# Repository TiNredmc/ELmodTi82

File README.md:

# ELmodTi82
EL backlight mod for TI-82. This Repo includes Schematic, PCB and BOMs.

# BOM (can be found cheaply on Aliexpress)
1. x1 HV823LG EL panel driver (https://www.aliexpress.com/item/4000117958037.html?spm=a2g0s.9042311.0.0.1d8e4c4dCgCwEE)
2. x1 1N4148 SOD-123 diode (https://www.aliexpress.com/item/32947085991.html?spm=a2g0s.12269583.0.0.7d003e51weey3z) select 1n4148 SOD-123
3. x1 10nF (0.01uF) 100V THT Polypropylene Film (https://www.aliexpress.com/item/4000051926991.html?spm=a2g0s.9042311.0.0.1d8e4c4dCgCwEE) select 10NF
4. x1 1nF 16V smd 0603 (https://www.aliexpress.com/item/33009930741.html?spm=a2g0s.9042311.0.0.1d8e4c4dCgCwEE) select 1nF
5. x1 750kOhm smd 0603 (https://www.aliexpress.com/item/32951328488.html?spm=a2g0s.9042311.0.0.1d8e4c4dCgCwEE) select 750k
6. x1 2MOhm smd 0603 (https://www.aliexpress.com/item/32951328488.html?spm=a2g0s.9042311.0.0.1d8e4c4dCgCwEE) Select 2M
7. x1 560uH 50mA smd 1812 (https://www.aliexpress.com/item/33036139022.html?spm=a2g0s.9042311.0.0.1d8e4c4dCgCwEE)
8. x1 10x10cm EL Panel (can be cut into the same size as the display, Will update later when I teardown my cal, roughtly 4cm x 6.5cm) (https://www.aliexpress.com/item/32689125682.html?spm=a2g0s.9042311.0.0.1d8e4c4dCgCwEE) 

# PCB
V1 https://oshpark.com/shared_projects/CnYBnhLE , V2 https://oshpark.com/shared_projects/YBjWS07Q

# UPDATE 1 (2020/3/5)
I just confused thinking that I order the SOD-123 but it's turn out to be SOD-323 which is smaller, but from online lookup on Google. they still some different but you (and me) can actually solder this tiny, by just put it in center and put LOADS of solder to hold it.

# UPDATE2 (2020/3/5)
I just confused again.... the SOD-123 is actually available and I order the SOD-123 🤦‍

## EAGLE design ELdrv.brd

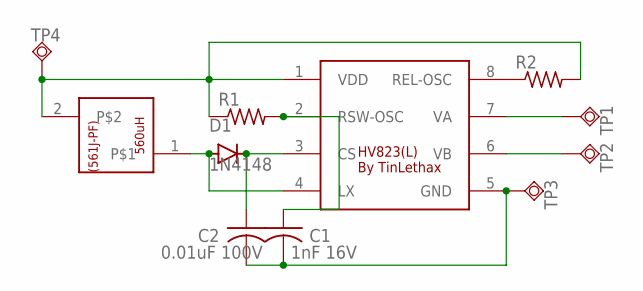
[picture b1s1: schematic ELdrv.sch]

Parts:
C1: 1nF 16V; C0603K
C2: 0.01uF 100V; C025-040X050
D1: 1N4148; SOD-123_MINI-SMA
R1, R2: R-US_R0603; R0603
TP1, TP2, TP3, TP4: TPSQTP20SQ; TP20SQ
U$1: HV823; SOIC127P600X175-9T200L
U$2: NL453232T-561J-PF; INDC4526X50N

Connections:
unnamed: D1.A, U$1.4 (LX), U$2.1
unnamed: C2.1, D1.C, U$1.3 (CS)
unnamed: R1.1, R2.2, TP4.TP, U$1.1 (VDD), U$2.2
unnamed: C1.1, R1.2, U$1.2 (RSW-OSC)
unnamed: R2.1, U$1.8 (REL-OSC)
unnamed: C1.2, C2.2, TP3.TP, U$1.5 (GND)
unnamed: TP1.TP, U$1.7 (VA)
unnamed: TP2.TP, U$1.6 (VB)

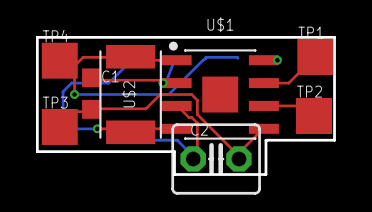
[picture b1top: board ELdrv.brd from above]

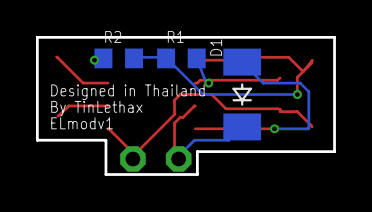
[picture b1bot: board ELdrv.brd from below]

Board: 2 copper layers, 16.5 x 7.6 mm, 11 parts (3 on the bottom side), 8 nets.

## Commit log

2020-03-03 added BOM and PCB
2020-03-03 schematic and board
2020-03-05 added the link for v2 and more
    -link for v2 board
    -link to but things same link with me (may died out soon. GO GET IT!)
2020-03-05 Update 1 ; Confusion.
2020-03-05 New v2
2020-03-06 update2
